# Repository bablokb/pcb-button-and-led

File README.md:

pcb-button-and-led
==================

This is a panel mountable pcb for 1-2 switches or LEDS.

Note that you can mount either an LED, or a button
on the left or right side. So this pcb supports
three different configurations.

For the LEDs you need 1206 LEDs and 1206 resistors
(on the back).

KiCAD sources are in `button-and-led.kicad`. Production
files for JLCPCB are in `production_files`.

License
-------

[![CC BY-SA 4.0][cc-by-sa-shield]][cc-by-sa]

This work is licensed under a
[Creative Commons Attribution-ShareAlike 4.0 International
License][cc-by-sa].

[![CC BY-SA 4.0][cc-by-sa-image]][cc-by-sa]

[cc-by-sa]: http://creativecommons.org/licenses/by-sa/4.0/
[cc-by-sa-image]: https://licensebuttons.net/l/by-sa/4.0/88x31.png
[cc-by-sa-shield]:
https://img.shields.io/badge/License-CC%20BY--SA%204.0-lightgrey.svg

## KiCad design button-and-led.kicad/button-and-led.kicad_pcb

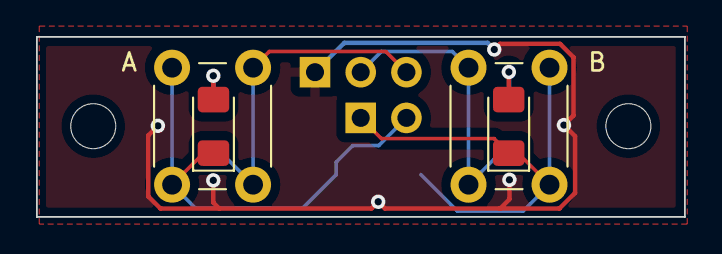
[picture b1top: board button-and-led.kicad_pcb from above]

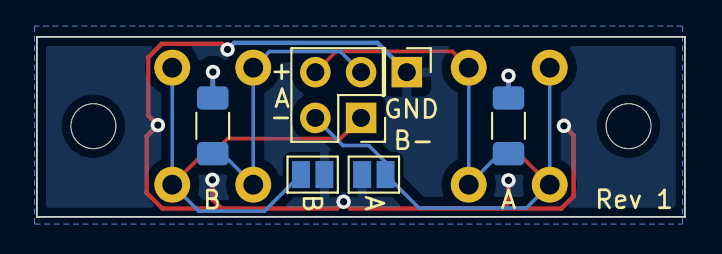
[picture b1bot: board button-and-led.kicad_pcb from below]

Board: 2 copper layers, 36.0 x 10.0 mm, 12 parts (6 on the bottom side), 7 nets.

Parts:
D1, D2: LED; LED_1206_3216Metric_Pad1.42x1.75mm_HandSolder
H1, H2: MountingHole; MountingHole_2.5mm
J1: Conn_GND; PinHeader_1x01_P2.54mm_Vertical
J2: Conn_Signal; PinHeader_2x02_P2.54mm_Vertical
JP1: Jmp_A_GND; SolderJumper-2_P1.3mm_Open_Pad1.0x1.5mm
JP2: Jmp_B_GND; SolderJumper-2_P1.3mm_Open_Pad1.0x1.5mm
R1, R2: R; R_1206_3216Metric_Pad1.30x1.75mm_HandSolder
SW1, SW2: SW_Push; SW_PUSH_6mm

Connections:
/A+: J2.4, R1.2, SW1.2
/A-: D1.1 (K), J2.2, JP1.1 (A), SW1.1
/B+: J2.3, R2.2, SW2.2
/B-: D2.1 (K), J2.1, JP2.1 (A), SW2.1
GND: J1.1, JP1.2 (B), JP2.2 (B)
unnamed: D1.2 (A), R1.1
unnamed: D2.2 (A), R2.1
